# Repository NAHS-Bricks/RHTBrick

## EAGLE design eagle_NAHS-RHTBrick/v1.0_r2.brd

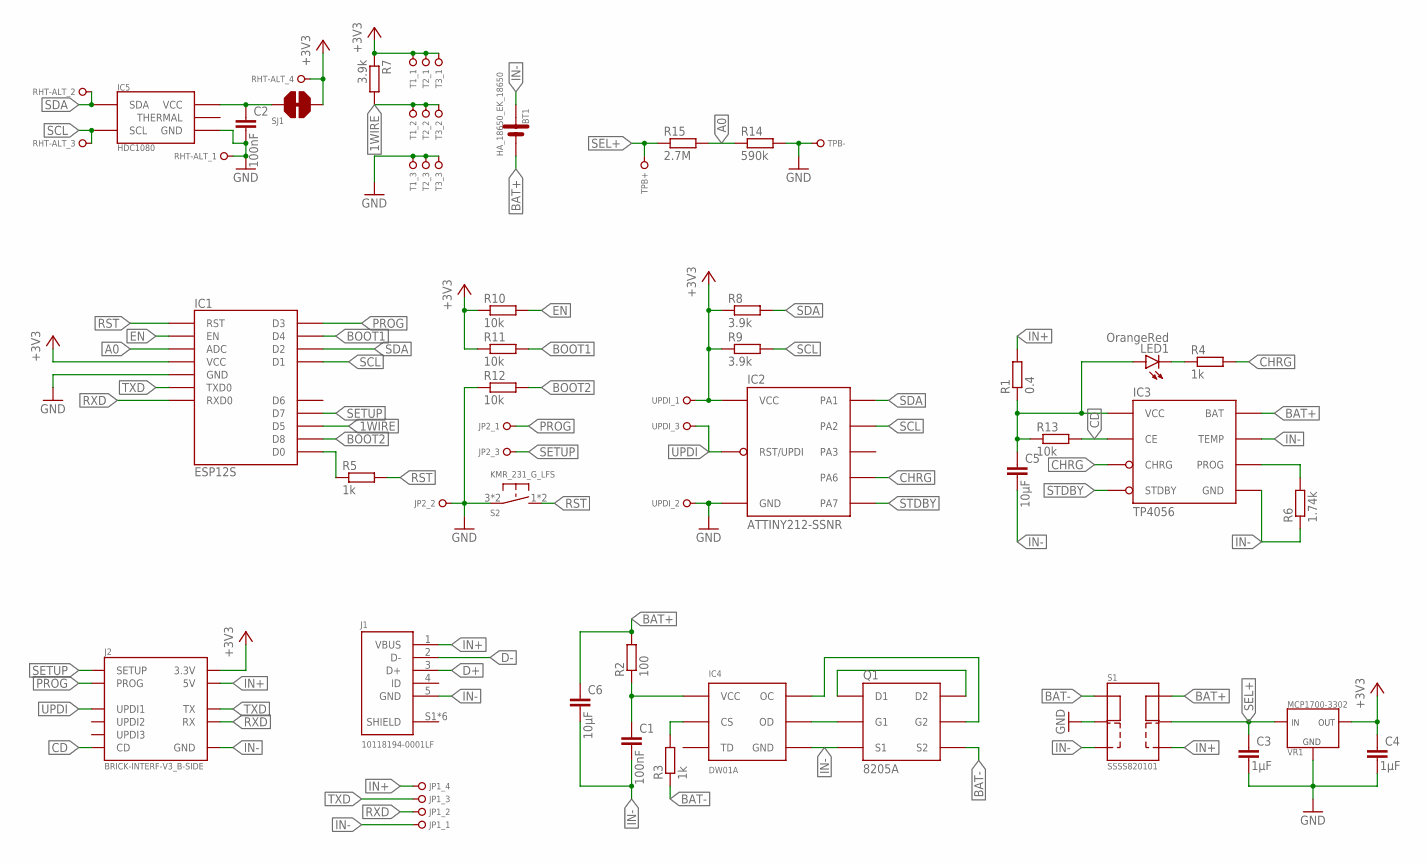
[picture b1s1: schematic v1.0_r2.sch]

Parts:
BT1: HA_18650_EK_18650
C1, C2: 100nF; C0805
C3, C4: 1µF; C0805
C5, C6: 10µF; C0805
IC1: ESP12S
IC2: ATTINY212-SSNR; SOIC8
IC3: TP4056; SO8-THERMALPAD
IC4: DW01A; SOT23-6
IC5: HDC1080
J1: 10118194-0001LF
J2: BRICK-INTERF-V3_B-SIDE; DF9-11P-1V(32)
JP1: PINHD_1X04_R_1; 1X04_R_1
JP2: PINHD_1X03_R_1; 1X03_R_1
LED1: OrangeRed; CHIP-LED0805
Q1: 8205A; TSSOP8
R1: 0.4; R0805
R2: 100; R0805
R3, R4, R5: 1k; R0805
R6: 1.74k; R0805
R7, R8, R9: 3.9k; R0805
R10, R11, R12, R13: 10k; R0805
R14: 590k; R0805
R15: 2.7M; R0805
RHT-ALT: PINHD_1X04_R_1; 1X04_R_1
S1: SSSS820101
S2: KMR_231_G_LFS
SJ1: SOLDERBRIDGE
T1, T2, T3: PINHD_1X03_R_1; 1X03_R_1
TPB+: PINHD_1X01_S_0.8; 1X01_S_0.8
TPB-: PINHD_1X01_S_0.8; 1X01_S_0.8
UPDI: PINHD_1X03_R_1; 1X03_R_1
VR1: MCP1700-3302; SOT23

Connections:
1WIRE: IC1.GPIO14 (D5), R7.2, T1.2, T2.2, T3.2
+3V3: C4.1, IC1.VCC, IC2.1 (VCC), J2.10 (3.3V), R7.1, R8.1, R9.1, R10.1, R11.1, RHT-ALT.4, SJ1.2, T1.1, T2.1, T3.1, UPDI.1, VR1.2 (OUT)
A0: IC1.ADC, R14.1, R15.2
BAT+: BT1.P1 (PLUS), BT1.P2 (PLUS), BT1.P3 (PLUS), C6.1, IC3.5 (BAT), R2.2, S1.6
BAT-: Q1.6 (S2), Q1.7 (S2), R3.1, S1.3
BOOT1: IC1.GPIO2 (D4), R11.2
BOOT2: IC1.GPIO15 (D8), R12.2
CD: IC3.8 (CE), J2.5 (CD), R13.2
CHRG: IC2.2 (PA6), IC3.7 (CHRG), R4.2
D+: J1.3 (D+)
D-: J1.2 (D-)
EN: IC1.EN, R10.2
GND: C2.2, C3.2, C4.2, IC1.GND, IC2.8 (GND), IC5.2 (GND), JP2.2, R12.1, R14.2, RHT-ALT.1, S1.2, S2.3 (2), S2.4 (2), T1.3, T2.3, T3.3, TPB-.1, UPDI.2, VR1.1 (GND)
IN+: J1.1 (VBUS), J2.4 (5V), JP1.4, R1.2, S1.4
IN-: BT1.M1 (MINUS), BT1.M2 (MINUS), BT1.M3 (MINUS), C1.2, C5.2, C6.2, IC3.1 (TEMP), IC3.3 (GND), IC3.T1 (GND), IC3.T2 (GND), IC3.T3 (GND), IC3.T4 (GND), IC3.T5 (GND), IC3.T6 (GND), IC3.T7 (GND), IC3.T8 (GND), IC4.6 (GND), J1.5 (GND), J2.6 (GND), JP1.1, Q1.2 (S1), Q1.3 (S1), R6.1, S1.1
unnamed: C5.1, IC3.4 (VCC), LED1.A, R1.1, R13.1
unnamed: IC3.2 (PROG), R6.2
unnamed: IC4.2 (CS), R3.2
unnamed: C1.1, IC4.5 (VCC), R2.1
unnamed: C2.1, IC5.5 (VCC), SJ1.1
unnamed: LED1.C, R4.1
unnamed: IC4.1 (OD), Q1.4 (G1)
unnamed: Q1.1 (D1), Q1.8 (D2)
unnamed: IC4.3 (OC), Q1.5 (G2)
PROG: IC1.GPIO0 (D3), J2.3 (PROG), JP2.1
RST: IC1.RST, R5.2, S2.1, S2.2 (1)
RXD: IC1.RXD0, J2.11 (RX), JP1.2
SCL: IC1.GPIO5 (D1), IC2.5 (PA2), IC5.6 (SCL), R9.2, RHT-ALT.3
SDA: IC1.GPIO4 (D2), IC2.4 (PA1), IC5.1 (SDA), R8.2, RHT-ALT.2
SEL+: C3.1, R15.1, S1.5, TPB+.1, VR1.3 (IN)
SETUP: IC1.GPIO13 (D7), J2.2 (SETUP), JP2.3
SHIELD: J1.S1 (SHIELD), J1.S2 (SHIELD), J1.S3 (SHIELD), J1.S4 (SHIELD), J1.S5 (SHIELD), J1.S6 (SHIELD)
STDBY: IC2.3 (PA7), IC3.6 (STDBY)
TXD: IC1.TXD0, J2.1 (TX), JP1.3
UPDI: IC2.6 (RST/UPDI), J2.7 (UPDI1), UPDI.3
WAKE: IC1.GPIO16 (D0), R5.1

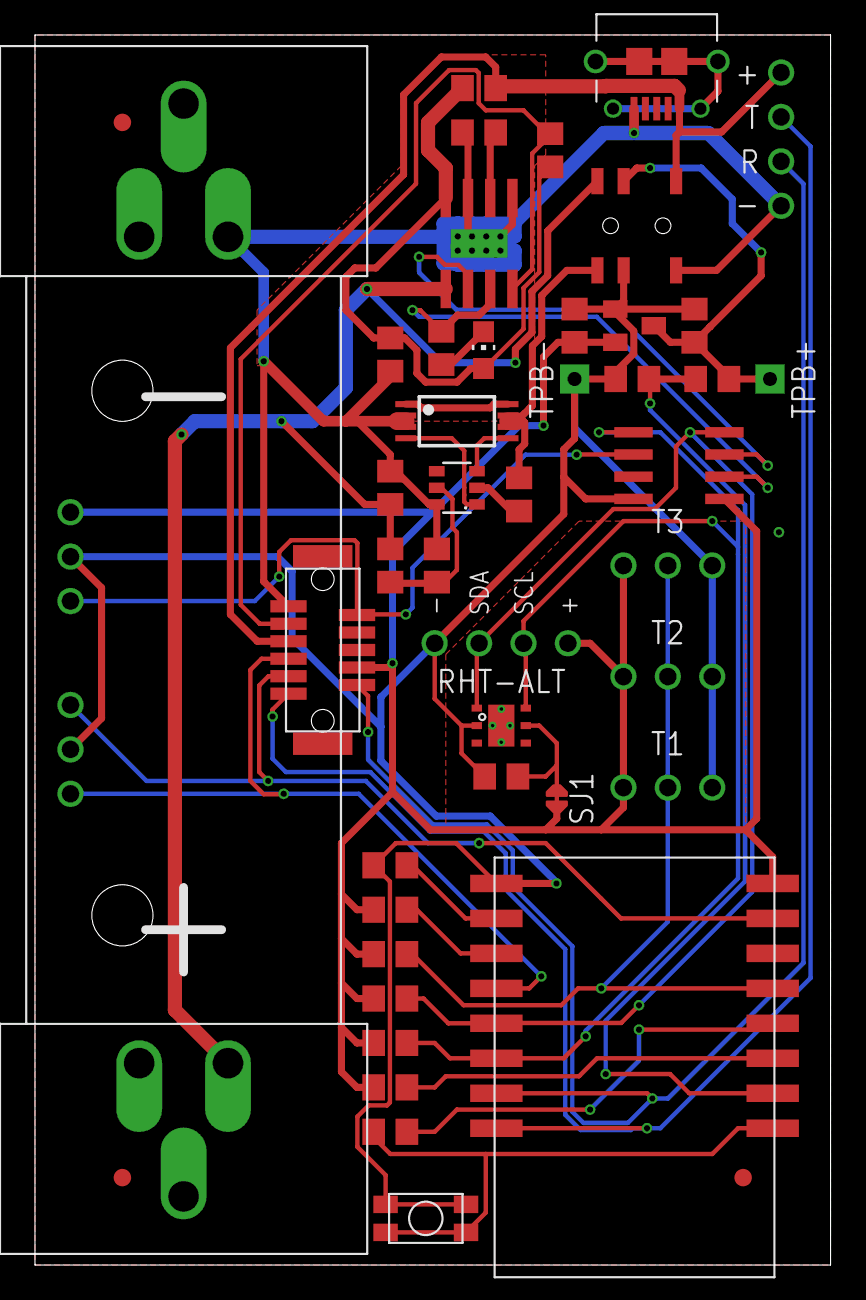
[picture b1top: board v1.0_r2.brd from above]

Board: 2 copper layers, 45.5 x 70.3 mm, 48 parts (1 on the bottom side), 34 nets.

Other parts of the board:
FD1, FD2, FD3: FIDUCIAL
U$1: BRICKS_LOGO_20

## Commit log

2021-08-09 begun v1.0 R1 Board
2021-08-09 saving
2021-08-10 v1.0 R1 Board done
2021-09-24 platformio project for v1 board
2021-10-05 v1.0 R2 Board
2021-10-14 v1.0 R2 Board done
2022-01-13 build-firmware invoker
2022-02-13 added ibom invoker and ibom for v1.0 r board
2022-12-01 v1.0 R3 Board done
2022-12-03 v1.0 R4 Board done
2022-12-03 added forgotten logo on v1.0 R4 Board
2022-12-09 replaced footprints with ones with custom paste mask on v1.0 R4 Board
2022-12-11 migrated firmware to new librarys
2022-12-30 started design of final v1.0 board
2023-01-02 forced firmware dependencies to support SHT4x sensors
2023-01-05 v1.0 Board - adjustments on bottom layer silkscreen
2024-01-11 v1.0 Board done; v1.0 Breakout Board done
2024-01-11 updated footprints for stencil
